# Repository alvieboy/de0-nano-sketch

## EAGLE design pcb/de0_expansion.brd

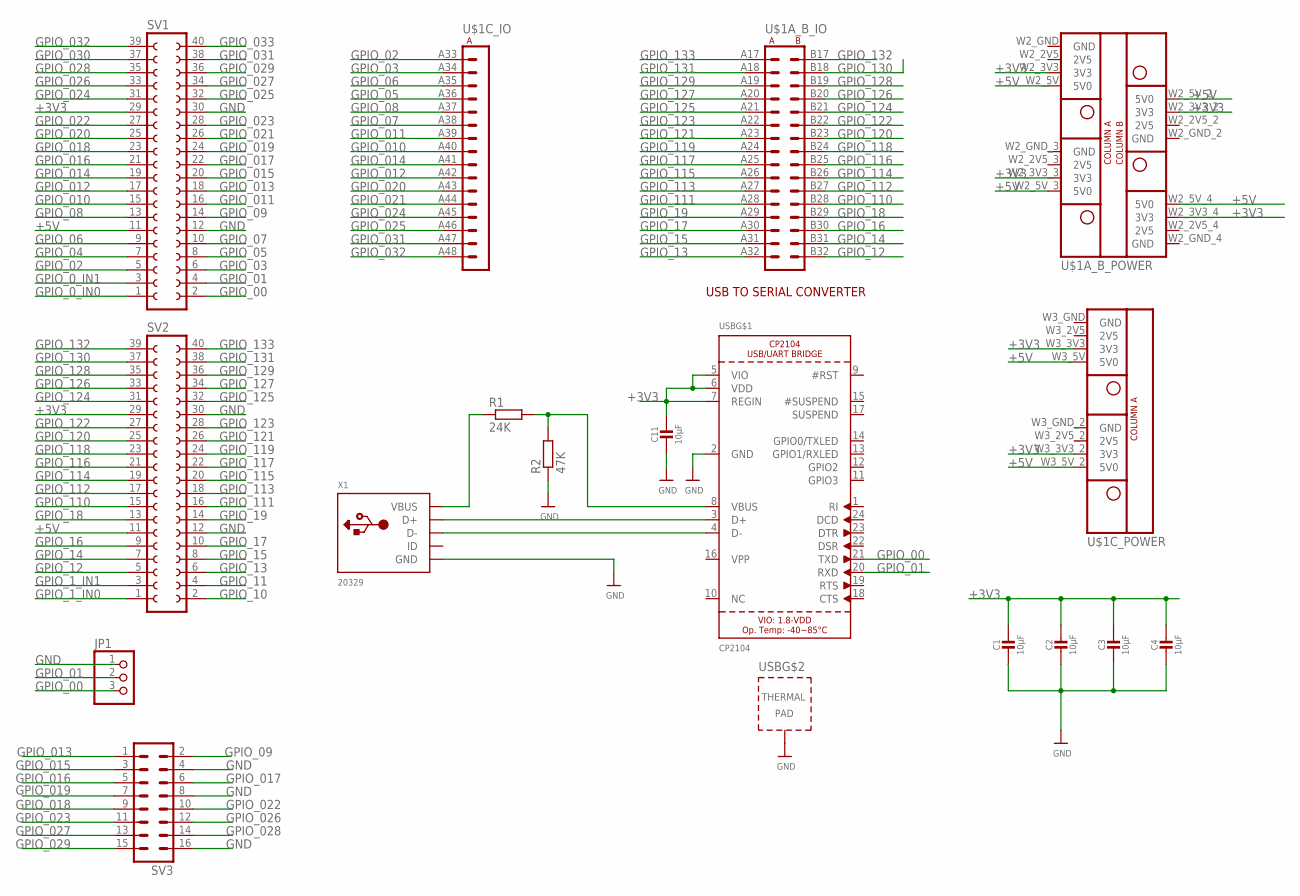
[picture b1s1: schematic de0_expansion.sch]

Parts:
C1, C2, C3, C4, C11: 10µF; 0805-NO; PARTNO CL21F106ZPFNNNE,Samsung,DK,1276-3012-1-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
JP1: PINHD-1X3; 1X03
R1: 24K; R0805W
R2: 47K; R0805W
SV1, SV2: FE20-2
SV3: ML16; PARTNO PRPC004DAAN-RC
U$1: MEGAWING_FULL_P1MEGAWING_P1; MEGAWING_FULL_NOHOLES_P1
USB: CP2104; QFN24_4MM_SMSC; PARTNO CP2104-F03-GM,Silicon Labs,dk,336-2008-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
X1: 20329; USB-MINIB_LARGER; PARTNO 10118193-0001LF,Amphenol,dk,609-4616-1-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

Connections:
+3V3: C1.1, C2.1, C3.1, C4.1, C11.1, SV1.29, SV2.29, U$1.W2_3V3 (3V3), U$1.W2_3V3_2 (3V3), U$1.W2_3V3_3 (3V3), U$1.W2_3V3_4 (3V3), U$1.W3_3V3 (3V3), U$1.W3_3V3_2 (3V3), USB.5 (VIO), USB.6 (VDD), USB.7 (REGIN)
+5V: SV1.11, SV2.11, U$1.W2_5V (5V0), U$1.W2_5V_2 (5V0), U$1.W2_5V_3 (5V0), U$1.W2_5V_4 (5V0), U$1.W3_5V (5V0), U$1.W3_5V_2 (5V0)
GND: C1.2, C2.2, C3.2, C4.2, C11.2, JP1.1, R2.1, SV1.12, SV1.30, SV2.12, SV2.30, SV3.4, SV3.8, SV3.16, U$1.W2_GND (GND), U$1.W2_GND_2 (GND), U$1.W2_GND_3 (GND), U$1.W2_GND_4 (GND), U$1.W3_GND (GND), U$1.W3_GND_2 (GND), USB.2 (GND), USB.THERM (TP), X1.GND
GPIO_00: JP1.3, SV1.2, USB.21 (TXD)
GPIO_0_IN0: SV1.1
GPIO_0_IN1: SV1.3
GPIO_01: JP1.2, SV1.4, USB.20 (RXD)
GPIO_1_IN0: SV2.1
GPIO_1_IN1: SV2.3
GPIO_02: SV1.5, U$1.A33 (A1)
GPIO_03: SV1.6, U$1.A34 (A2)
GPIO_04: SV1.7
GPIO_05: SV1.8, U$1.A36 (A4)
GPIO_06: SV1.9, U$1.A35 (A3)
GPIO_07: SV1.10, U$1.A38 (A6)
GPIO_08: SV1.13, U$1.A37 (A5)
GPIO_09: SV1.14, SV3.2
GPIO_010: SV1.15, U$1.A40 (A8)
GPIO_10: SV2.2
GPIO_011: SV1.16, U$1.A39 (A7)
GPIO_11: SV2.4
GPIO_012: SV1.17, U$1.A42 (A10)
GPIO_12: SV2.5, U$1.B32 (B16)
GPIO_013: SV1.18, SV3.1
GPIO_13: SV2.6, U$1.A32 (A16)
GPIO_014: SV1.19, U$1.A41 (A9)
GPIO_14: SV2.7, U$1.B31 (B15)
GPIO_015: SV1.20, SV3.3
GPIO_15: SV2.8, U$1.A31 (A15)
GPIO_016: SV1.21, SV3.5
GPIO_16: SV2.9, U$1.B30 (B14)
GPIO_017: SV1.22, SV3.6
GPIO_17: SV2.10, U$1.A30 (A14)
GPIO_018: SV1.23, SV3.9
GPIO_18: SV2.13, U$1.B29 (B13)
GPIO_019: SV1.24, SV3.7
GPIO_19: SV2.14, U$1.A29 (A13)
GPIO_020: SV1.25, U$1.A43 (A11)
GPIO_021: SV1.26, U$1.A44 (A12)
GPIO_022: SV1.27, SV3.10
GPIO_023: SV1.28, SV3.11
GPIO_024: SV1.31, U$1.A45 (A13)
GPIO_025: SV1.32, U$1.A46 (A14)
GPIO_026: SV1.33, SV3.12
GPIO_027: SV1.34, SV3.13
GPIO_028: SV1.35, SV3.14
GPIO_029: SV1.36, SV3.15
GPIO_030: SV1.37
GPIO_031: SV1.38, U$1.A47 (A15)
GPIO_032: SV1.39, U$1.A48 (A16)
GPIO_033: SV1.40
GPIO_110: SV2.15, U$1.B28 (B12)
GPIO_111: SV2.16, U$1.A28 (A12)
GPIO_112: SV2.17, U$1.B27 (B11)
GPIO_113: SV2.18, U$1.A27 (A11)
GPIO_114: SV2.19, U$1.B26 (B10)
GPIO_115: SV2.20, U$1.A26 (A10)
GPIO_116: SV2.21, U$1.B25 (B9)
GPIO_117: SV2.22, U$1.A25 (A9)
GPIO_118: SV2.23, U$1.B24 (B8)
GPIO_119: SV2.24, U$1.A24 (A8)
GPIO_120: SV2.25, U$1.B23 (B7)
GPIO_121: SV2.26, U$1.A23 (A7)
GPIO_122: SV2.27, U$1.B22 (B6)
GPIO_123: SV2.28, U$1.A22 (A6)
GPIO_124: SV2.31, U$1.B21 (B5)
GPIO_125: SV2.32, U$1.A21 (A5)
GPIO_126: SV2.33, U$1.B20 (B4)
GPIO_127: SV2.34, U$1.A20 (A4)
GPIO_128: SV2.35, U$1.B19 (B3)
GPIO_129: SV2.36, U$1.A19 (A3)
GPIO_130: SV2.37, U$1.B18 (B2)
GPIO_131: SV2.38, U$1.A18 (A2)
GPIO_132: SV2.39, U$1.B17 (B1)
GPIO_133: SV2.40, U$1.A17 (A1)
unnamed: R1.2, R2.2, USB.8 (VBUS)
unnamed: USB.3 (D+), X1.D+
unnamed: R1.1, X1.VBUS
unnamed: USB.4 (D-), X1.D-

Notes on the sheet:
USB TO SERIAL CONVERTER

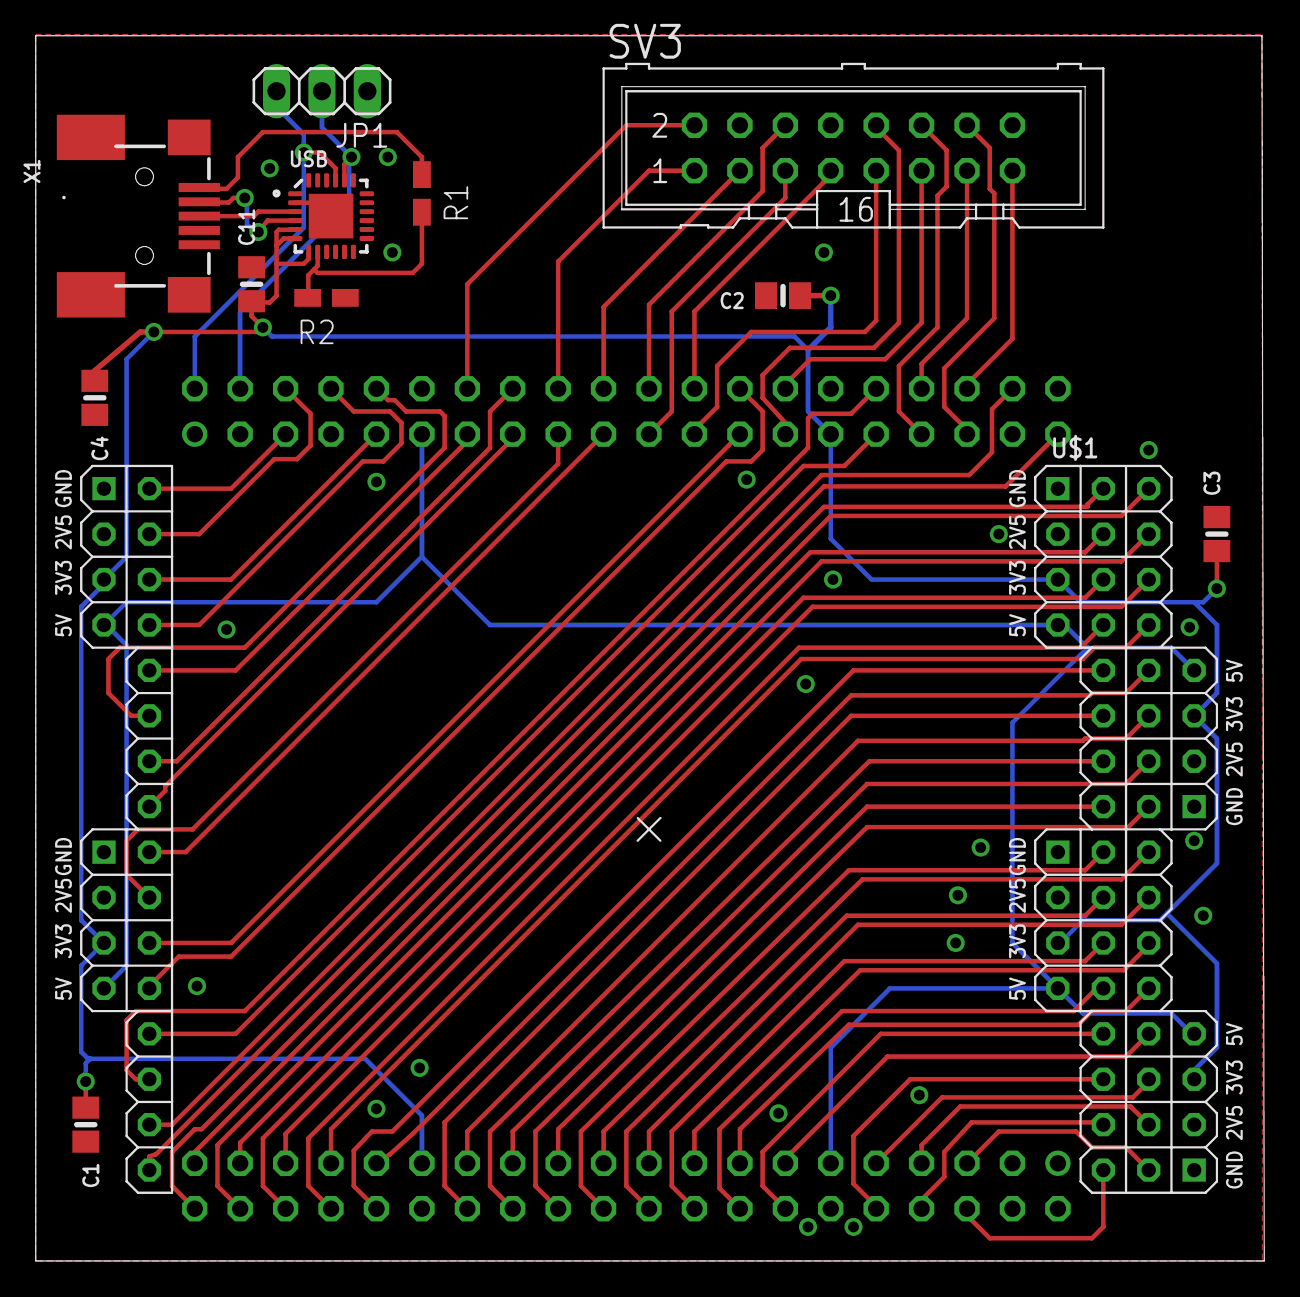
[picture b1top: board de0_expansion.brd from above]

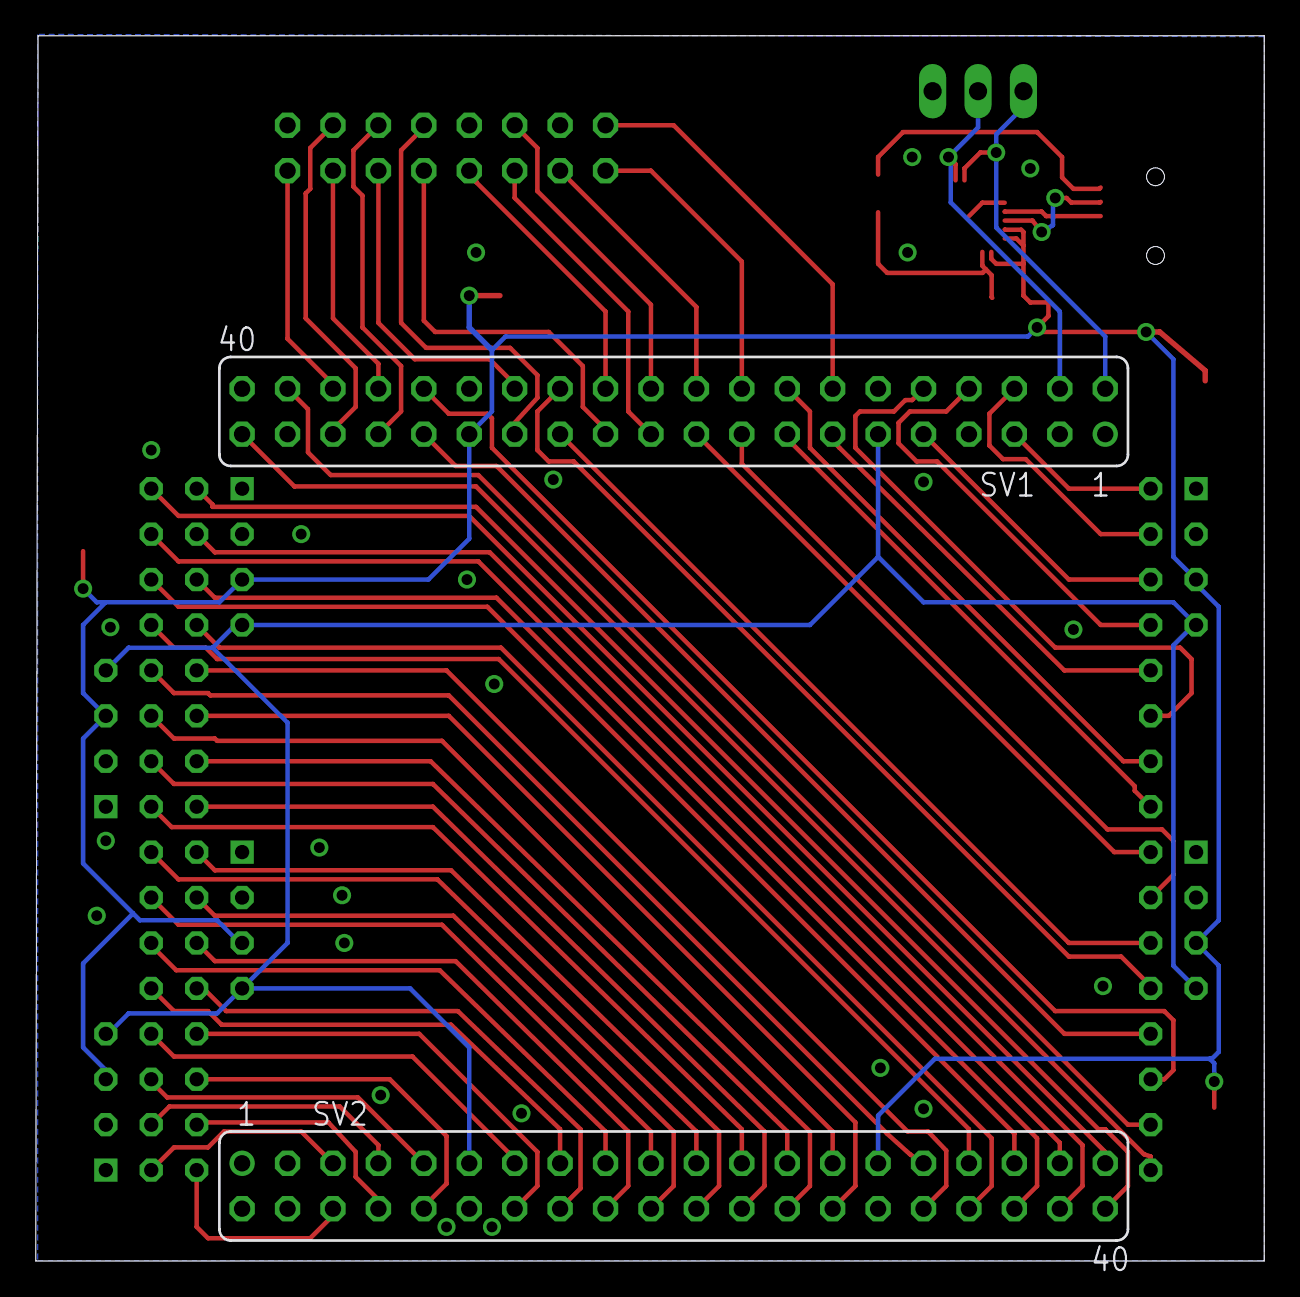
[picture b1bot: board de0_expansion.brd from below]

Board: 2 copper layers, 68.7 x 68.5 mm, 14 parts (2 on the bottom side), 70 nets.

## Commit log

2017-09-17 Import sources
2017-09-17 Add FFT and window, remove panel extern
2017-09-18 1st demo version
2017-09-18 Add missing files
2017-09-25 Move sketch into proper place
2017-09-25 Add PCB

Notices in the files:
parts and their libraries:
microbuilder: This work is placed in the public domain, and may be freely used for commercial and non-commercial work with the following conditions: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
